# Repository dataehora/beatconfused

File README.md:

# BeatConfused

A small web studio of fast, elegant, install-free music tools. Every tool
is plain HTML, CSS and vanilla JavaScript with the Web Audio API — no build
step, no dependencies, no accounts, works offline after first load.

Live at [beatconfused.com](https://beatconfused.com).

## Tools

| Tool | Path | What it does |
| --- | --- | --- |
| **Metronome** | [`/metronome/`](https://beatconfused.com/metronome/) | Tap tempo, organized time signatures, beat subdivisions, counting modes, sound styles, and pulse / number / pendulum visuals. |
| **Tuner** | [`/tuner/`](https://beatconfused.com/tuner/) | Chromatic instrument tuner with needle, strobe and LED-meter displays, an adjustable A4 reference pitch, historical tuning standards, a test-tone generator, and a spectrum analyser. |
| **Octave Strobe Tuner** | [`/strobetuner/`](https://beatconfused.com/strobetuner/) | Identifies the note being played and shows its tuning across every octave at once on a single strobe disc. |
| **Chromatic Strobe Tuner** | [`/multistrobe/`](https://beatconfused.com/multistrobe/) | One dedicated strobe wheel per note, laid out like a piano keyboard, each with a ring per octave across the 88-key range. |
| **Luthier Tuning** | [`/luthier/`](https://beatconfused.com/luthier/) | Live spectrogram for luthiers and tuners: a slowly decaying live spectrum over a peak-hold record of every frequency, a sustain waterfall, harmonic guides, and a full-range / audible-only toggle. |

## Repository layout

```
index.html            Studio landing page (tool cards + JSON-LD)
styles.css             Landing-page styles
metronome/             Metronome — index.html, script.js, styles.css, Assets/
tuner/                 Tuner — index.html, script.js, styles.css
strobetuner/           Octave Strobe Tuner — index.html, script.js, styles.css
multistrobe/           Chromatic Strobe Tuner — index.html, script.js, styles.css
luthier/               Luthier Tuning (spectrogram) — index.html, script.js, styles.css
etutti/                eTutti (work in progress, unlisted) — Web MIDI page, Teensy firmware/,
                       hardware/ (eTuttino board v0.7 + case SPEC v9), manuais/, models/
binfacevsfarage/       Standalone browser game (not linked from the studio)
shared/                Assets shared across tools
CNAME, robots.txt, sitemap.xml   Hosting + crawl metadata
```

## Metronome controls

### Tempo
- **Slider** / **input field** — smooth or direct BPM entry (40–240)
- **+/- buttons** — step by 5 BPM
- **Tap tempo** — tap the button or press `T` to detect BPM
- **Arrow keys** — Up / Down to adjust BPM

### Beat settings
- **Time signature** — organized simple, compound and odd meters
- **Beat subdivision** — split each beat into more pulses
- **Tempo counting** — beat count, measure + beat, or hidden
- **Beat visual** — pulse, numbers, or pendulum
- **Sound style** — electronic, bossa, jazz, wood, cymbal, cowbell
- **Sound / vibration toggles** and **volume control**

### Keyboard shortcuts
- **Space** — start / stop
- **Arrow Up / Down** — BPM ±5
- **T** — tap tempo

### Custom sounds
Drop `{style}_{accent|beat|subdivision}` audio files (`.mp3`, then `.ogg`,
then `.wav`) into `metronome/Assets/` and they replace the synthesised click
for that combination. Anything not supplied keeps the built-in sound, so the
metronome always has audio even with no custom assets.

## Tuner controls

- **Start Tuner** — vintage-style slide switch above the display; turns the
  microphone on. A "no signal" sign appears below the display after ~3s of
  silence while running.
- **Display** — needle, strobe or LED meter
- **Input Monitor and Test Tone** — collapsed by default; microphone gain
  boost and a live level meter, plus a pure tone (with its own frequency,
  fine-tuning and volume controls) fed straight into the tuner and the
  speakers, no mic needed — the same panel /strobetuner/ and /multistrobe/
  use too
- **Spectrum Analyser** — vintage or modern style
- **Tuning Standard and Reference Pitch** — Equal Temperament plus
  Vallotti, Young II, 1/4-comma meantone and Just Intonation (each built
  from first principles), and an A4 reference from 392–466 Hz with
  historical presets (French Baroque, Baroque, Verdi, Standard, Modern,
  Italian Renaissance)
- **Frequency Table** — every note of an 88-key piano (octaves down the
  rows, notes across the columns) under the selected Tuning Standard and
  Reference Pitch, with a live cents deviation next to whichever note is
  sounding

## Luthier Tuning controls

- **Start Listening** — the same slide switch as the tuners (or `Space`)
- **Full range / Audible only** — everything the microphone captures (up
  to half its sample rate, with infrasound and ultrasound shaded) or just
  20 Hz – 20 kHz
- **Live curve** — the current spectrum; each frequency falls back at the
  **Decay speed** (dB/s) so a note's ring-out stays visible
- **Peak hold** — the pale-blue background graph: the loudest level each
  frequency has reached since the last **Reset peak hold**. **On** keeps
  it until reset; **Temporary** holds each maximum for 2 s, then lets it
  fall at the same Decay speed as the live curve; **Off** hides it
- **Sustain history** — a 12-second waterfall under the display
- **Cursor** — hover / tap for frequency, nearest note, live and peak dB,
  plus dashed guides at 2×, 3×, 4×… to judge inharmonicity
- **Input gain** — boosts quiet instruments

## Technical stack

- **HTML5 / CSS3** — semantic structure, gradients and animations
- **Web Audio API** — high-precision timing, autocorrelation pitch
  detection, Goertzel per-octave analysis for the strobe tools
- **Vanilla JavaScript** — no dependencies, no build step
- **Structured data + crawl files** — JSON-LD, `robots.txt`, `sitemap.xml`

## Development

Everything is static — serve the repo root with any static file server:

```bash
git clone https://github.com/dataehora/beatconfused.git
cd beatconfused
python3 -m http.server 8000
# then open http://localhost:8000/
```

## Deployment

Served via GitHub Pages on the `beatconfused.com` domain (`CNAME`). Any
static host with HTTPS works — no server-side code.

## License

MIT License — feel free to use and modify.

## Contributing

Contributions are welcome. Please open a Pull Request.

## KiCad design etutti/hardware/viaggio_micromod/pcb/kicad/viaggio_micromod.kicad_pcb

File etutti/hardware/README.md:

# eTuttino — PCB design (Hall-effect, velocity-sensitive)

A 44-key chromatic button-accordion controller (C-griff, G3–E6).

- **Keys:** Gateron magnetic (Hall-effect) switches, MX-compatible.
- **Sensing:** a TI DRV5056A3 linear Hall sensor under every key, so the
  firmware knows how far down each key is, and from how fast it went
  down, the note's velocity.
- **Brain:** a Teensy 4.0 with the PJRC Audio Adaptor Board Rev D stacked
  on it.

The firmware is in [`../firmware`](../firmware), the web page is
[beatconfused.com/etutti](https://beatconfused.com/etutti/), and the case
(Seixo / Madeira, SPEC v9; shape frozen since v7) is in [`case/`](case/).

> **Board v0.7 (this one) is made for the SPEC v7–v9 case.** The keys sit
> on the case's hexagonal grid (18.5 mm pitch), and the board takes the
> case's inner outline. The assembly and user manuals in
> [`../manuais`](../manuais/) describe this board, the case and the
> controls board; their pictures come from
> [`manual3d/`](manual3d/) (Blender). Nothing has been built
> yet: only the firmware has run on a real Teensy + Audio Board.

## Ordering (ready to upload)

Generated, routed and checked: KiCad DRC 0 errors, 0 warnings,
0 unconnected; firmware cross-check 44/44.

| File | Upload it as |
| --- | --- |
| [`fab/etuttino_gerbers.zip`](fab/etuttino_gerbers.zip) | **the PCB**: Gerbers + drill files. 2 layers, FR-4, **1.2 mm**, shaped outline (328 × 97 mm bounding box) |
| [`fab/etuttino_bom.csv`](fab/etuttino_bom.csv) + [`fab/etuttino_cpl_bottom.csv`](fab/etuttino_cpl_bottom.csv) | **assembly** (JLCPCB PCBA, *Bottom Side*): every SMD part is on the back |
| [`fab/etuttino_plate_gerbers.zip`](fab/etuttino_plate_gerbers.zip) | **the switch plate**: a copper-less **1.6 mm** FR-4 board with the 14 mm cutouts, cut to the case's plate outline (the case is drawn for 1.6 since SPEC v8) |
| [`fab/etuttino_controls_gerbers.zip`](fab/etuttino_controls_gerbers.zip) | **the controls board**: 2 layers, FR-4 1.6 mm, 41.5 × 25.5 mm, all through-hole (see below) |
| [`case/out/`](case/out/) | **the case** (STEP + STL) and the button caps; see [`case/README.md`](case/README.md) |

The BOM has LCSC numbers for the JLCPCB basic parts. Match the two TI parts
(`DRV5056A3QDBZR`, `CD74HC4067M96`) by manufacturer part number in
JLCPCB's BOM tool. Check every part's rotation in the placement preview
before paying.

## Why the sensors are on the back

The DRV5056 is unipolar: its output only rises when a **south** pole faces
its marked (top) side. Gateron's magnetic switches have the magnet's
**north** pole facing down, so a sensor on the front, facing up, would read
nothing.

On the back, the sensor faces away from the switch. The field reaches it
through the board from behind, and the sensor reads that as positive. A
1.2 mm board keeps the sensor as close to the magnet as that allows.

The A3 variant (30 mV/mT at 3.3 V, about 80 mT before saturation) leaves
headroom against Gateron's ~10 mT at rest and ~90 mT bottomed out. The A4
also works.

## Source files and regenerating

| File | What it is |
| --- | --- |
| [`case/pcb_envelope.py`](case/pcb_envelope.py) → `case/out/pcb_envelope.json` | the room the case leaves for the board: outline (notched round the case's screw bosses), plate outline, bottom-plate pillars, height levels, key centres, the stack's and J3's places. Run with the CadQuery venv (see `case/README.md`) |
| [`generate.py`](generate.py) | reads that envelope. Single source of the key layout and of the sensor → multiplexer map (plain Python 3). Prints the `KEY_INPUT` table for the firmware |
| [`build_pcb.py`](build_pcb.py) | builds and **routes** the KiCad board inside that outline, runs DRC, checks it against the firmware, exports everything in `fab/` |
| [`controls_pcb.py`](controls_pcb.py) | the controls board: places, routes (the same router), DRCs and exports it |
| [`mechanics.py`](mechanics.py) | how far the board bends under a key press on the case's pillars (KiCad's Python, numpy) |
| [`manual3d/`](manual3d/) | the assembly manual's pictures: photo-like renders and numbered line drawings of every step, made in Blender from the case STLs, both KiCad boards (`kicad-cli` GLB) and a library of datasheet-sized parts (`parts.py`). `build.py` runs it all; the visual standard and the balloon numbers are in [`manual3d/STYLE.md`](manual3d/STYLE.md) |
| [`etuttino.pretty/`](etuttino.pretty) | footprint library: `Gateron_Magnetic_MX_1u` (two 1.75 mm peg holes, no centre post, no pins), origin at the switch centre |
| [`kicad/etuttino.kicad_pcb`](kicad/etuttino.kicad_pcb), [`kicad/etuttino_plate.kicad_pcb`](kicad/etuttino_plate.kicad_pcb) | the routed board and the plate |
| `build/etuttino_pcb_preview.svg`, `build/etuttino_keys.csv`, `build/etuttino_plate.dxf` | preview; each key's switch, sensor, multiplexer channel, Teensy pin, note and X/Y; the plate as DXF (for aluminium) |

After a case change, rebuild in this order:

```bash
C:/Users/julia/.venvs/cadquery/Scripts/python.exe case/case.py
C:/Users/julia/.venvs/cadquery/Scripts/python.exe case/pcb_envelope.py
python generate.py
"C:/Program Files/KiCad/10.0/bin/python.exe" build_pcb.py
"C:/Program Files/KiCad/10.0/bin/python.exe" mechanics.py
```

Each routing attempt takes about four minutes. The router is greedy: if
a net can't be routed, the script starts again with that net first, up to
20 times. `DEFAULT_ROUTE_FIRST` keeps the order that worked
(`OUT_U41,OUT_U42,GND,LED_R,LED_G_DRV,OUT_U34` for v0.6 and v0.7).

`build_pcb.py` exits with an error if any of these happens:

- DRC finds a problem.
- Anything is left unconnected.
- A part on the back sits over one of the bottom plate's pillars.
- A key doesn't reach the multiplexer channel and Teensy pin that the
  firmware's tables give.

It writes the routed channels into the sketch's `KEY_INPUT`.

## Layout

Chromatic accordion, C-griff, on a **hexagonal grid**: every button is
**18.5 mm** from its six neighbours, and the rows are 18.5 × cos 30° =
**16.02 mm** apart.

- Each key along a row is a **minor third (3 semitones)** above the
  previous one. A diagonal step to the next row is **one semitone**.
- Row 4 repeats row 1's notes from A3 to C6, on row 2's columns.
- **Row 1 is nearest the player.** It is at the front edge, which is the
  bottom of KiCad's top view.
- The same switches also play **B-griff**: the web page's C/B-griff
  switch sends CC 24, and the firmware swaps rows 1 and 3. The PCB does
  not change.

| Row | Keys | Notes | y (mm) |
| --- | --- | --- | --- |
| 1 | 11 | A3 C4 D♯4 F♯4 A4 C5 D♯5 F♯5 A5 C6 D♯6 | 74.03 |
| 2 | 12 | G3 A♯3 C♯4 E4 G4 A♯4 C♯5 E5 G5 A♯5 C♯6 E6 | 58.01 |
| 3 | 11 | G♯3 B3 D4 F4 G♯4 B4 D5 F5 G♯5 B5 D6 | 41.99 |
| 4 | 10 | A3 C4 D♯4 F♯4 A4 C5 D♯5 F♯5 A5 C6 | 25.97 |

**Coordinates** are the case SPEC's. x is measured from the case's left
face, y towards the player. That is KiCad's top view as it stands.

**The board** is the case's inner cavity less 0.5 mm, notched round the
nine screw columns. It fits both the Seixo (2.5 mm walls) and the Madeira
(4 mm). On the left it runs under the interface area, where the Teensy +
Audio Board stack sits in the back corner:

- USB faces the case's left face, where a short cable goes to the panel
  socket.
- The VIN row is at the back.
- The stack is ~13 mm tall in the eTuttino and 10 mm or less in the
  eTuttiChorus.
- The Audio Board sits ~3 mm above the PCB on its header legs.
- These positions come from `case/fit_check.py`.

**Held by the case:**

- Under the keys, the lid presses the plate's edge, the plate presses
  the switches, and the switches' bottom housings press the board.
- Under the interface, two M2 screws come up from below. They go through
  the bottom plate's pillars at (30; 60) and (12; 70) and through the
  board's holes H1 and H2, with a nut on top. These two pillars are
  Ø6, with a counterbore for the head. The router keeps copper 3.5 mm
  away from both holes.
- The board rests on **64 pillars** of the bottom plate, one at the
  centre of every triangle of three neighbouring keys (10.7 mm from each
  sensor). The case has 3 more pillars under the interface.
- Under a firm 3 N press the board sags **0.044 mm** at worst (E6, row 2)
  and 0.009 mm on average. Check with `mechanics.py`.
- No part on the back may sit over a pillar. `build_pcb.py` checks this.

## Electrical

**Per key (back side):**

- A DRV5056A3 (SOT-23) straight under the switch centre.
- Its 100 nF capacitor just behind it.
- A 3.3 V bus behind each key row and a GND bus in front of it (0.4 mm).
- The sensor output drops to a via and is routed to its multiplexer.

**Multiplexers:** three CD74HC4067 (SOIC-24), all on the back.

- U51 sits in front of the interface, left of rows 1 and 2. It serves row 1
  and the left end of row 2.
- U52 and U53 lie sideways in the strip behind row 4 and serve the rest,
  split left and right.
- The router picks each key's channel; see `build/etuttino_keys.csv`.
- The address lines are shared, and Enable is tied to GND.

| Net | Teensy pin |
| --- | --- |
| SEL0–SEL3 (multiplexer address S0–S3) | 0, 1, 2, 3 |
| COM0 / COM1 / COM2 (U51 / U52 / U53 output) | 14 (A0) / 15 (A1) / 16 (A2) |
| VIN (USB 5 V) → regulator | VIN |
| GND | GND (both rows) |
| LED_R_DRV / LED_G_DRV → 330 Ω (R1 / R2) → J3 | 4 (red), 5 (green) |
| POT → J3 | 22 (A8) |
| ENC_A / ENC_B / ENC_SW → J3 | 17 / 9 / 6 |

**J3, the controls board.** A JST PH 2.0 mm 8-pin vertical header, in front
of the Audio Board, under the interface lid. A short 1:1 cable goes up
to the controls board.

| Pin | Net |
| --- | --- |
| 1 | VCC 3.3 V |
| 2 | GND |
| 3 | POT |
| 4 | ENC_A |
| 5 | ENC_B |
| 6 | ENC_SW |
| 7 | LED_R |
| 8 | LED_G |

The firmware reads the pot as the volume and the encoder as the
instrument selector (see `../firmware/README.md`). With no controls board
plugged in, the pot input is ignored. Pin 6 is the Audio Board's optional
memory-chip select, so leave that chip unfitted.

## Controls board

`controls_pcb.py` → `kicad/etuttino_controls.kicad_pcb` and
`fab/etuttino_controls_gerbers.zip`. KiCad DRC 0 / 0 / 0. In case
coordinates it spans x 14.5–56, y 35.5–61. It hangs under the interface lid
on two posts of the case, with M2 screws through H1 and H2 from below. Its
top faces the lid:

| Ref | Part | Where |
| --- | --- | --- |
| RV1 | Alps RK09K vertical pot, 10 k linear, 6 mm shaft L = 15 | shaft at (20; 45): volume |
| SW1 | Alps EC11E encoder with push switch, L = 15 | shaft at (37; 45): instrument |
| D1 | 3 mm red/green LED, common cathode | (52; 45), on a spacer up to the lid's hole (Seixo) or just under the light pipe (Madeira); `case/FIT_CHECK.md` gives the spacer length |
| J1 | JST PH B8B-PH-K vertical, on the back, facing down | the cable drops straight to the main board's J3, pin for pin |

The encoder's common and one switch leg go to GND. The Teensy's pull-ups
do the rest. The LED's 330 Ω resistors are on the main board.

**Power LED.** A 3 mm red/green bicolour LED (common cathode) on the
controls board, under the lid's LED hole, or the Madeira's light pipe:

- orange while the keys are read at power-up;
- green while playing;
- blinking red on an error.

**Power.** 44 sensors draw about 260 mA, more than the Teensy's own 3.3 V
pin should give. An AMS1117-3.3 (U60, SOT-223) makes a separate 3.3 V rail
from VIN for the sensors and the multiplexers:

- it sits on the back between the Teensy pin rows;
- it has 10 µF in and 22 µF out.

**Pins kept clear of:**

- 7, 8, 18–21, 23: the Audio Board's audio and I²C;
- 10–13: its SD card;
- 15 is its *optional* volume pot, which is not fitted on a stock board, so
  COM1 can use it.

**Routing:** two layers.

- Per-key wiring and the row buses are laid deterministically.
- Everything else goes through a small A* grid router in `build_pcb.py`:
  0.254 mm grid aligned to the Teensy pins, both layers, vias, KiCad's
  clearances, 0.5 mm from the board's outline.
- KiCad's DRC then checks the result independently.

## Teensy + Audio Board mounting

- Two rows of 14 holes (2.54 mm pitch, 15.24 mm apart), with the 0–12 row
  at the front and the VIN–13 row at the back. The silkscreen marks
  "GND"/"0", "VIN"/"23" and "< USB".
- Two 1×14 extra-long male headers (≈ 20–25 mm pins) join all three
  boards: the Teensy is soldered straight onto the Audio Board, the
  header's plastic as the only spacer, and the long legs go on down
  through these holes with the Audio Board ~3 mm above the PCB, soldered
  and trimmed on the back.
- Stack height, from under the Audio Board to the top of the Teensy's
  USB: the case was checked with 13 mm and has room for 16.9 mm (Seixo) /
  16.4 mm (Madeira); the eTuttiChorus needs 10 mm or less, to clear the
  screen.
- USB goes to the panel socket through a short cable with a 90° micro-USB
  plug. The panel headphone jack is wired to the Audio Board's headphone
  pads.

## Bill of materials (main board)

| Qty | Part | Notes |
| --- | --- | --- |
| 44 | Gateron KS-20 magnetic switch (north pole down) | plate-mounted, **not soldered**: no pins, two plastic pegs |
| 44 | DRV5056A3QDBZR, SOT-23 | back, under each switch |
| 47 | 100 nF 0805 | one per sensor + one per multiplexer |
| 3 | CD74HC4067M96, SOIC-24 | back |
| 1 | AMS1117-3.3, SOT-223 | back |
| 1 + 1 | 10 µF, 22 µF 0805 | regulator input / output |
| 2 | 330 Ω 0805 | LED resistors R1, R2 (back) |
| 1 | JST PH 8-pin vertical header (B8B-PH-K-S) + a 1:1 PH cable, ~60 mm | J3, to the controls board |
| 2 + 2 | M2 × 10 mm screw + M2 nut | through the bottom plate's two thick pillars and H1 / H2 |
| 1 | Teensy 4.0 + PJRC Audio Adaptor Board **Rev D** | + 2 × 1×14 extra-long male headers |
| 1 | switch plate | 1.6 mm FR-4 from `fab/etuttino_plate_gerbers.zip`, or 1.5 mm aluminium from `build/etuttino_plate.dxf` |
| 44 | button caps | 3D-printed from `case/out/keycap_*.stl` (26 natural / C-F, 18 sharp) |

**Controls board:**

| Qty | Part |
| --- | --- |
| 1 | Alps RK09K1130 (or equivalent) vertical pot, 10 k linear, 15 mm shaft |
| 1 | Alps EC11E with push switch, **15 pulses / 15 detents**, 15 mm shaft (`ENC_STEPS_PER_DETENT` = 4 in the firmware; 2 for a 30-detent one) |
| 1 | 3 mm LED, red/green, common cathode, + a ≈ 4 mm LED spacer (Seixo); the Madeira has a 3 mm light pipe in the lid instead |
| 1 | JST PH B8B-PH-K-S |
| 2 | M2 × 5 mm self-tapping screws, into the lid's posts |
| 2 | knobs, Ø9, for 6 mm shafts |

The case is listed in [`case/README.md`](case/README.md).

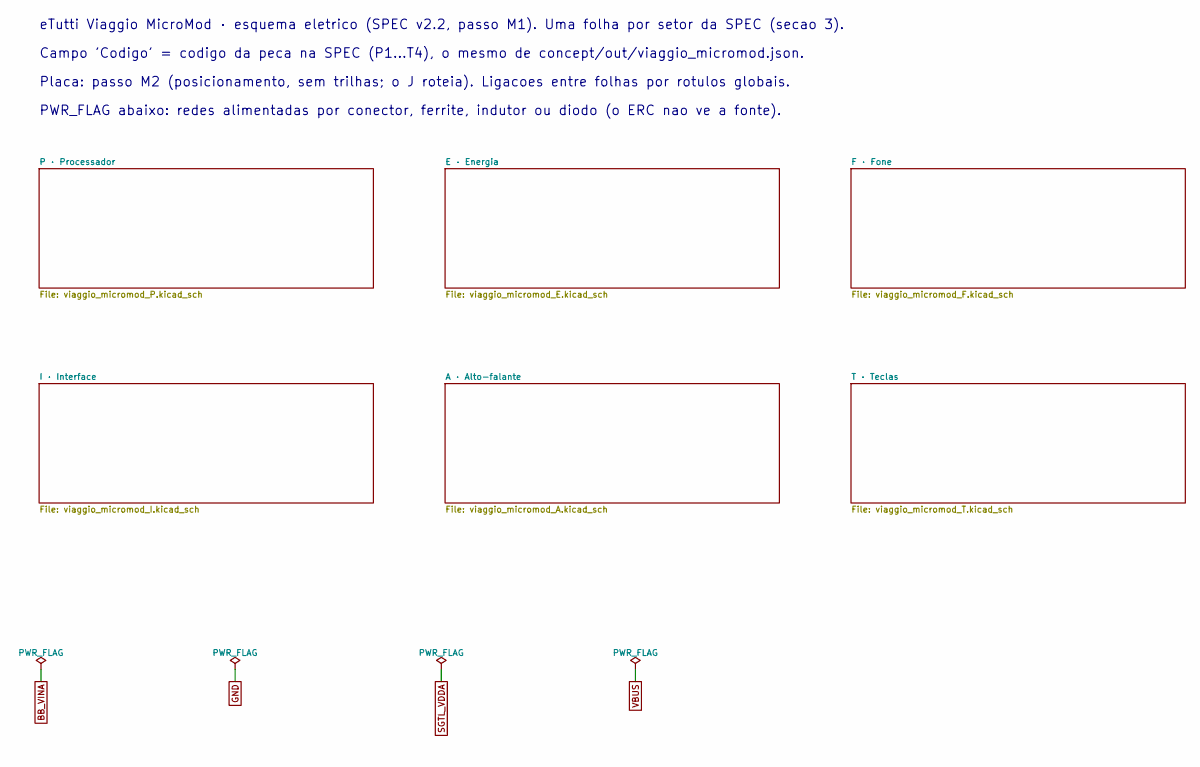
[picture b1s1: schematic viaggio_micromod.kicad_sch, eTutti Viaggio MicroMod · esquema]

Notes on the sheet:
eTutti Viaggio MicroMod · esquema eletrico (SPEC v2.2, passo M1). Uma folha por setor da SPEC (secao 3).
Campo 'Codigo' = codigo da peca na SPEC (P1...T4), o mesmo de concept/out/viaggio_micromod.json.
Placa: passo M2 (posicionamento, sem trilhas; o J roteia). Ligacoes entre folhas por rotulos globais.
PWR_FLAG abaixo: redes alimentadas por conector, ferrite, indutor ou diodo (o ERC nao ve a fonte).

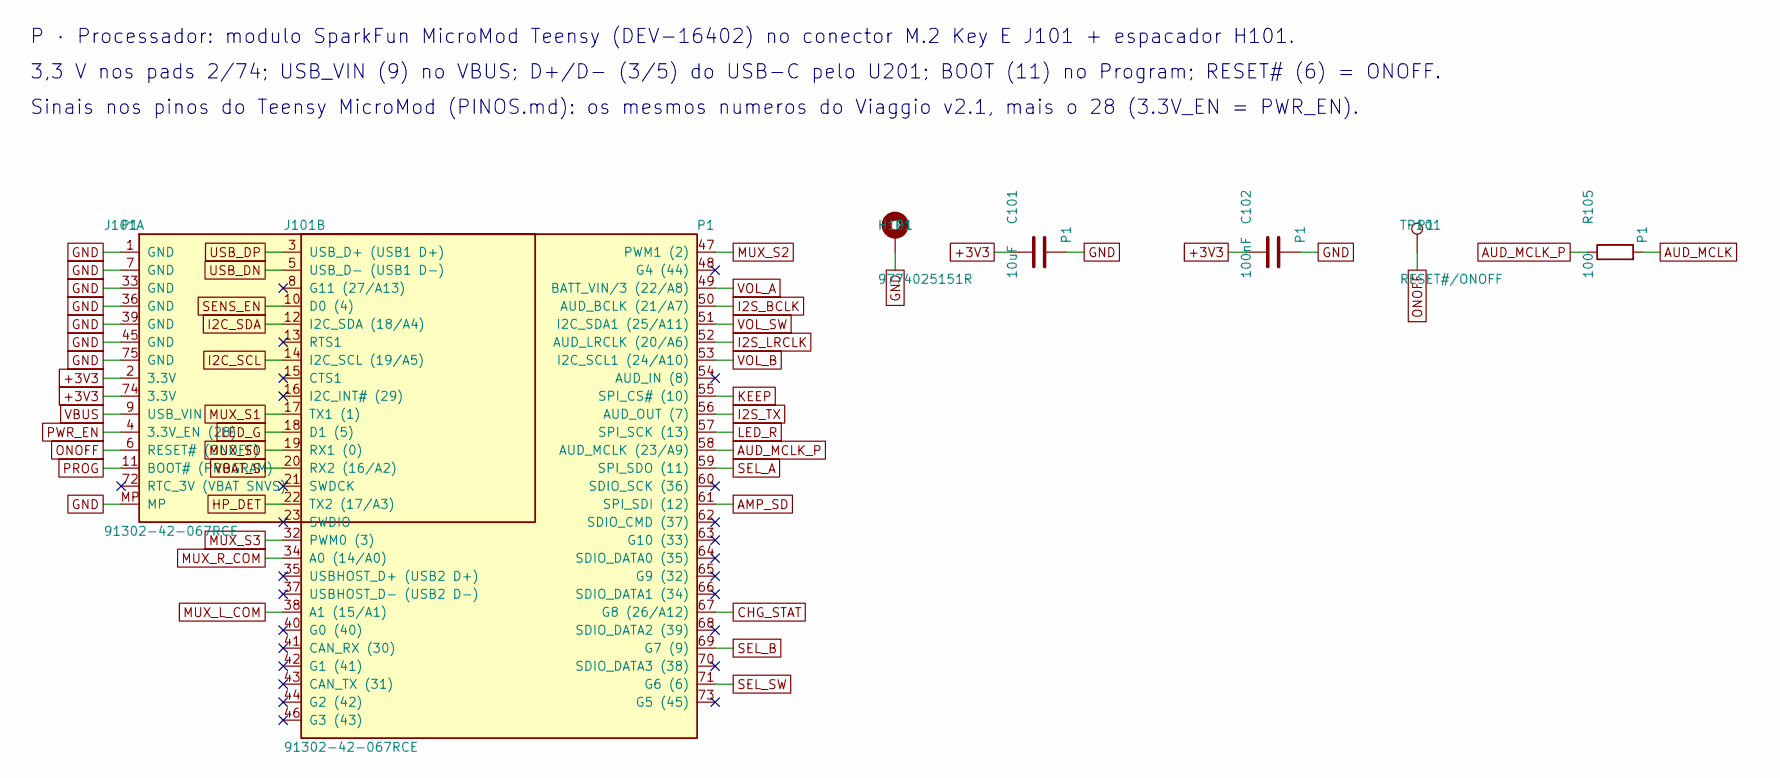
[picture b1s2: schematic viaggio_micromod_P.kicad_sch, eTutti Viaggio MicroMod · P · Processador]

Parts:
C101: 10uF; C_0805_2012Metric; LCSC C15850
C102: 100nF; C_0402_1005Metric; LCSC C1525
H101: 9774025151R; Standoff_SMD_M2.5_H2.5
J101: 91302-42-067RCE; M.2_E_H4.2_UMAX_91302-42-067; LCSC C48985906
R105: 100; R_0402_1005Metric; LCSC C25076
TP101: RESET#/ONOFF; TestPoint_Pad_D1.5mm

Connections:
+3V3: C101.1, C102.1, J101.2 (3.3V), J101.74 (3.3V); also elsewhere on the board
AMP_SD: J101.61 (SPI_SDI (12)); also elsewhere on the board
AUD_MCLK: R105.2; also elsewhere on the board
AUD_MCLK_P: J101.58 (AUD_MCLK (23/A9)), R105.1
CHG_STAT: J101.67 (G8 (26/A12)); also elsewhere on the board
GND: C101.2, C102.2, H101.1, J101.1 (GND), J101.7 (GND), J101.33 (GND), J101.36 (GND), J101.39 (GND), J101.45 (GND), J101.75 (GND), J101.MP; also elsewhere on the board
HP_DET: J101.22 (TX2 (17/A3)); also elsewhere on the board
I2C_SCL: J101.14 (I2C_SCL (19/A5)); also elsewhere on the board
I2C_SDA: J101.12 (I2C_SDA (18/A4)); also elsewhere on the board
I2S_BCLK: J101.50 (AUD_BCLK (21/A7)); also elsewhere on the board
I2S_LRCLK: J101.52 (AUD_LRCLK (20/A6)); also elsewhere on the board
I2S_TX: J101.56 (AUD_OUT (7)); also elsewhere on the board
KEEP: J101.55 (SPI_CS# (10)); also elsewhere on the board
LED_G: J101.18 (D1 (5)); also elsewhere on the board
LED_R: J101.57 (SPI_SCK (13)); also elsewhere on the board
MUX_L_COM: J101.38 (A1 (15/A1)); also elsewhere on the board
MUX_R_COM: J101.34 (A0 (14/A0)); also elsewhere on the board
MUX_S0: J101.19 (RX1 (0)); also elsewhere on the board
MUX_S1: J101.17 (TX1 (1)); also elsewhere on the board
MUX_S2: J101.47 (PWM1 (2)); also elsewhere on the board
MUX_S3: J101.32 (PWM0 (3)); also elsewhere on the board
ONOFF: J101.6 (RESET# (ONOFF)), TP101.1; also elsewhere on the board
PROG: J101.11 (BOOT# (PROGRAM)); also elsewhere on the board
PWR_EN: J101.4 (3.3V_EN (28)); also elsewhere on the board
SEL_A: J101.59 (SPI_SDO (11)); also elsewhere on the board
SEL_B: J101.69 (G7 (9)); also elsewhere on the board
SEL_SW: J101.71 (G6 (6)); also elsewhere on the board
SENS_EN: J101.10 (D0 (4)); also elsewhere on the board
USB_DN: J101.5 (USB_D- (USB1 D-)); also elsewhere on the board
USB_DP: J101.3 (USB_D+ (USB1 D+)); also elsewhere on the board
VBAT_S: J101.20 (RX2 (16/A2)); also elsewhere on the board
VBUS: J101.9 (USB_VIN); also elsewhere on the board
VOL_A: J101.49 (BATT_VIN/3 (22/A8)); also elsewhere on the board
VOL_B: J101.53 (I2C_SCL1 (24/A10)); also elsewhere on the board
VOL_SW: J101.51 (I2C_SDA1 (25/A11)); also elsewhere on the board

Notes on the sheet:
P · Processador: modulo SparkFun MicroMod Teensy (DEV-16402) no conector M.2 Key E J101 + espacador H101.
3,3 V nos pads 2/74; USB_VIN (9) no VBUS; D+/D- (3/5) do USB-C pelo U201; BOOT (11) no Program; RESET# (6) = ONOFF.
Sinais nos pinos do Teensy MicroMod (PINOS.md): os mesmos numeros do Viaggio v2.1, mais o 28 (3.3V_EN = PWR_EN).

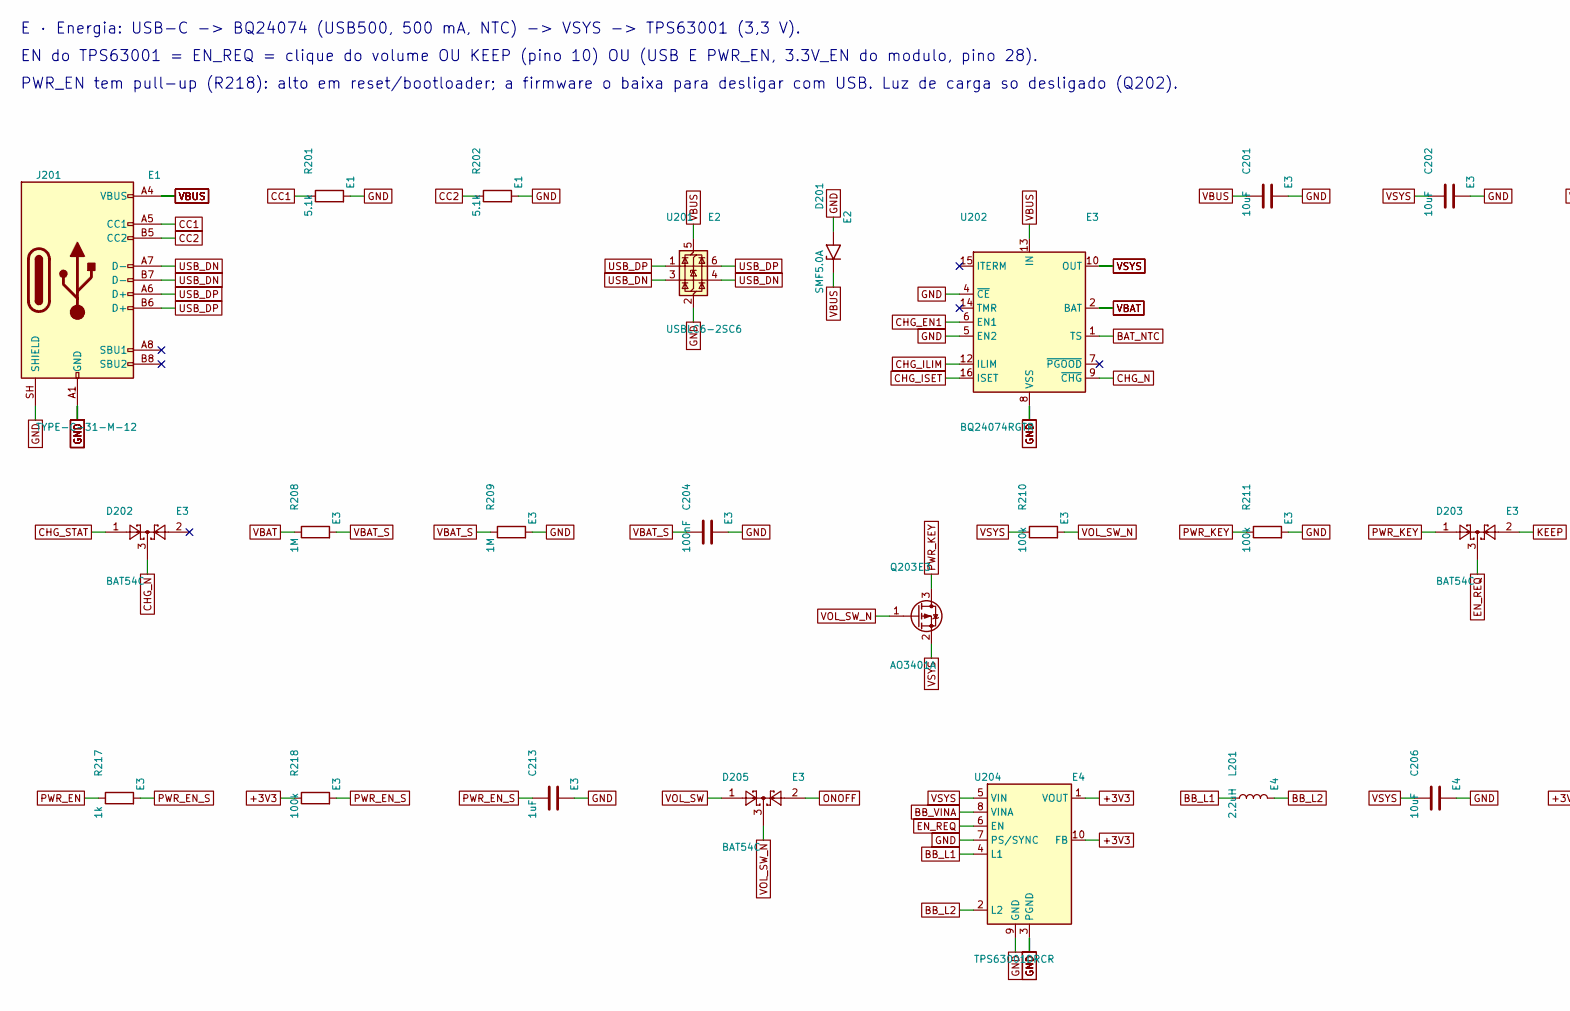
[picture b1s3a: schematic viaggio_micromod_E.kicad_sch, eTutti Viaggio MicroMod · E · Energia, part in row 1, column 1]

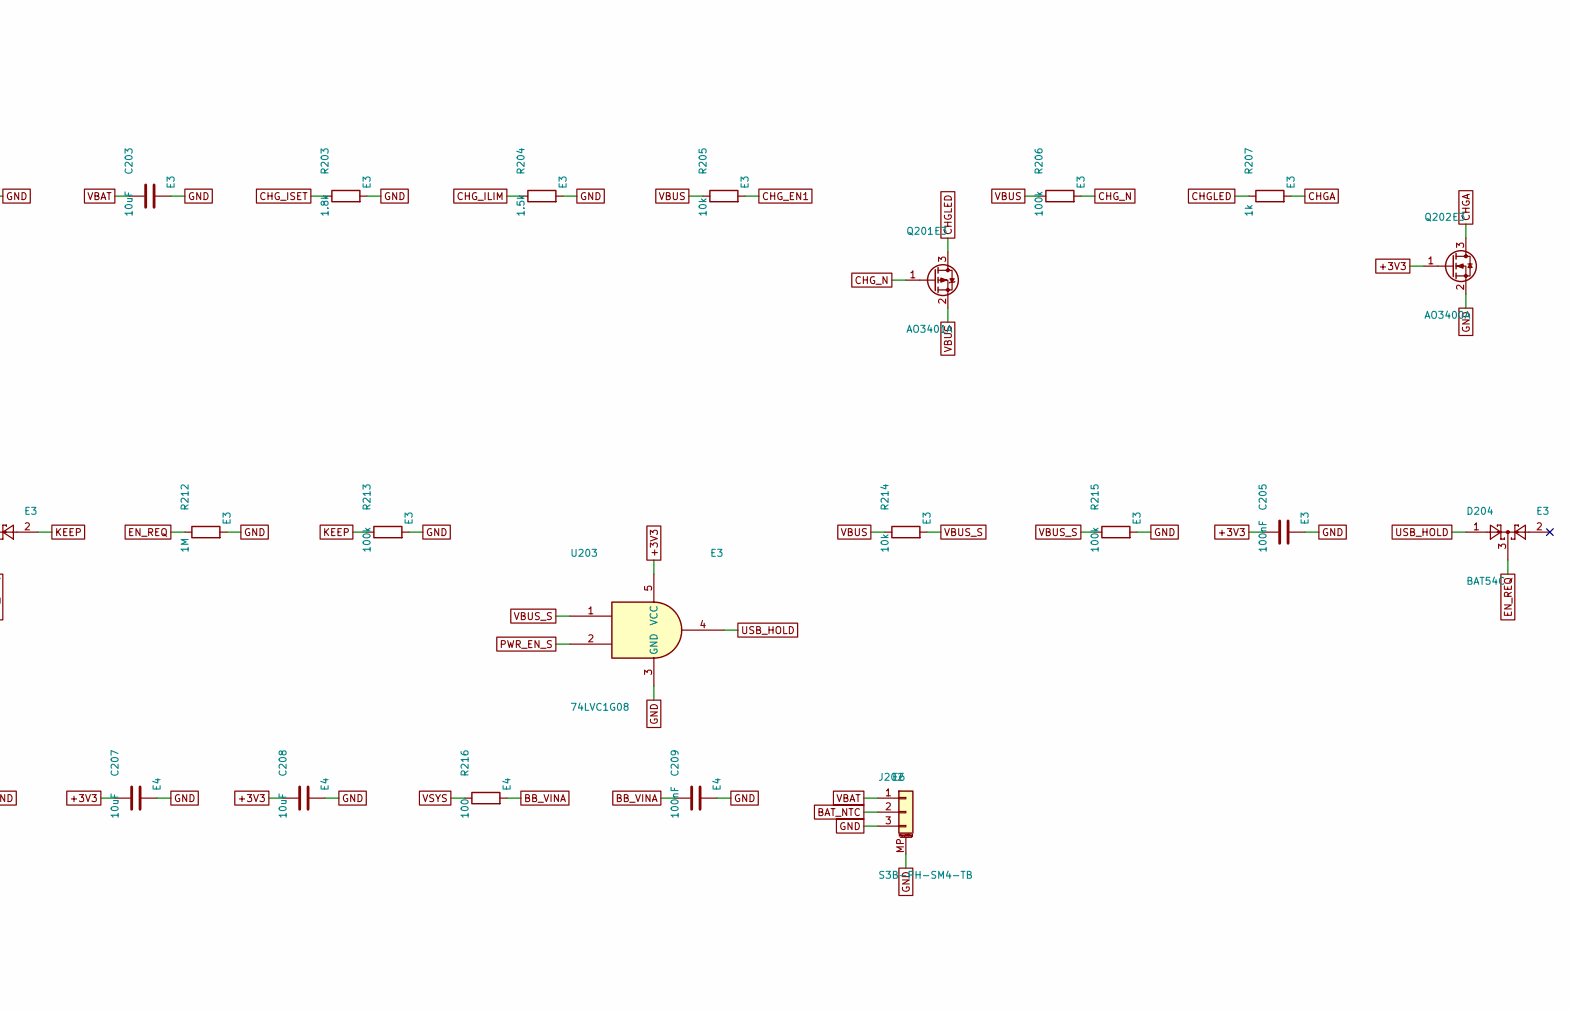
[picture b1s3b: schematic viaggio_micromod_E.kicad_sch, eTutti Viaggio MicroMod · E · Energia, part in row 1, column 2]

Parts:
C201, C202, C203, C206, C207, C208: 10uF; C_0805_2012Metric; LCSC C15850
C204, C205, C209: 100nF; C_0402_1005Metric; LCSC C1525
C213: 1uF; C_0402_1005Metric; LCSC C52923
D201: SMF5.0A; D_SOD-123F; LCSC C151296
D202, D203, D204, D205: BAT54C; SOT-23; LCSC C134405
J201: TYPE-C-31-M-12; USB_C_Receptacle_HRO_TYPE-C-31-M-12; LCSC C165948
J202: S3B-PH-SM4-TB; JST_PH_S3B-PH-SM4-TB_1x03-1MP_P2.00mm_Horizontal; LCSC C265101
L201: 2.2uH; L_Changjiang_FNR4020S; LCSC C167825
Q201, Q203: AO3401A; SOT-23; LCSC C15127
Q202: AO3400A; SOT-23; LCSC C20917
R201, R202: 5.1k; R_0402_1005Metric; LCSC C25905
R203: 1.8k; R_0402_1005Metric; LCSC C25811
R204: 1.5k; R_0402_1005Metric; LCSC C25867
R205, R214: 10k; R_0402_1005Metric; LCSC C25744
R206, R210, R211, R213, R215, R218: 100k; R_0402_1005Metric; LCSC C25741
R207, R217: 1k; R_0402_1005Metric; LCSC C11702
R208, R209, R212: 1M; R_0402_1005Metric; LCSC C26083
R216: 100; R_0402_1005Metric; LCSC C25076
U201: USBLC6-2SC6; SOT-23-6; LCSC C7519
U202: BQ24074RGTR; VQFN-16-1EP_3x3mm_P0.5mm_EP1.6x1.6mm; LCSC C54313
U203: 74LVC1G08; SOT-23-5; LCSC C7666
U204: TPS63001DRCR; Texas_DRC0010J; LCSC C28060

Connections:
+3V3: C205.1, C207.1, C208.1, Q202.1 (G), R218.1, U203.5 (VCC), U204.1 (VOUT), U204.10 (FB); also elsewhere on the board
BAT_NTC: J202.2, U202.1 (TS)
BB_L1: L201.1, U204.4 (L1)
BB_L2: L201.2, U204.2 (L2)
BB_VINA: C209.1, R216.2, U204.8 (VINA)
CC1: J201.A5 (CC1), R201.1
CC2: J201.B5 (CC2), R202.1
CHGA: Q202.3 (D), R207.2; also elsewhere on the board
CHGLED: Q201.3 (D), R207.1
CHG_EN1: R205.2, U202.6 (EN1)
CHG_ILIM: R204.1, U202.12 (ILIM)
CHG_ISET: R203.1, U202.16 (ISET)
CHG_N: D202.3, Q201.1 (G), R206.2, U202.9 (~CHG)
CHG_STAT: D202.1; also elsewhere on the board
EN_REQ: D203.3, D204.3, R212.1, U204.6 (EN)
GND: C201.2, C202.2, C203.2, C204.2, C205.2, C206.2, C207.2, C208.2, C209.2, C213.2, D201.2 (A2), J201.A1 (GND), J201.A12 (GND), J201.B1 (GND), J201.B12 (GND), J201.SH (SHIELD), J202.3, J202.MP (MountPin), Q202.2 (S), R201.2, R202.2, R203.2, R204.2, R209.2, R211.2, R212.2, R213.2, R215.2, U201.2 (GND), U202.4 (~CE), U202.5 (EN2), U202.8 (VSS), U202.17 (VSS), U203.3 (GND), U204.3 (PGND), U204.7 (PS/SYNC), U204.9 (GND), U204.11 (PGND); also elsewhere on the board
KEEP: D203.2, R213.1; also elsewhere on the board
ONOFF: D205.2; also elsewhere on the board
PWR_EN: R217.1; also elsewhere on the board
PWR_EN_S: C213.1, R217.2, R218.2, U203.2
PWR_KEY: D203.1, Q203.3 (D), R211.1
USB_DN: J201.A7 (D-), J201.B7 (D-), U201.3 (I/O2), U201.4 (I/O2); also elsewhere on the board
USB_DP: J201.A6 (D+), J201.B6 (D+), U201.1 (I/O1), U201.6 (I/O1); also elsewhere on the board
USB_HOLD: D204.1, U203.4
VBAT: C203.1, J202.1, R208.1, U202.2 (BAT), U202.3 (BAT)
VBAT_S: C204.1, R208.2, R209.1; also elsewhere on the board
VBUS: C201.1, D201.1 (A1), J201.A4 (VBUS), J201.A9 (VBUS), J201.B4 (VBUS), J201.B9 (VBUS), Q201.2 (S), R205.1, R206.1, R214.1, U201.5 (VBUS), U202.13 (IN); also elsewhere on the board
VBUS_S: R214.2, R215.1, U203.1
VOL_SW: D205.1; also elsewhere on the board
VOL_SW_N: D205.3, Q203.1 (G), R210.2; also elsewhere on the board
VSYS: C202.1, C206.1, Q203.2 (S), R210.1, R216.1, U202.10 (OUT), U202.11 (OUT), U204.5 (VIN); also elsewhere on the board

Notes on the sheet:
E · Energia: USB-C -> BQ24074 (USB500, 500 mA, NTC) -> VSYS -> TPS63001 (3,3 V).
EN do TPS63001 = EN_REQ = clique do volume OU KEEP (pino 10) OU (USB E PWR_EN, 3.3V_EN do modulo, pino 28).
PWR_EN tem pull-up (R218): alto em reset/bootloader; a firmware o baixa para desligar com USB. Luz de carga so desligado (Q202).

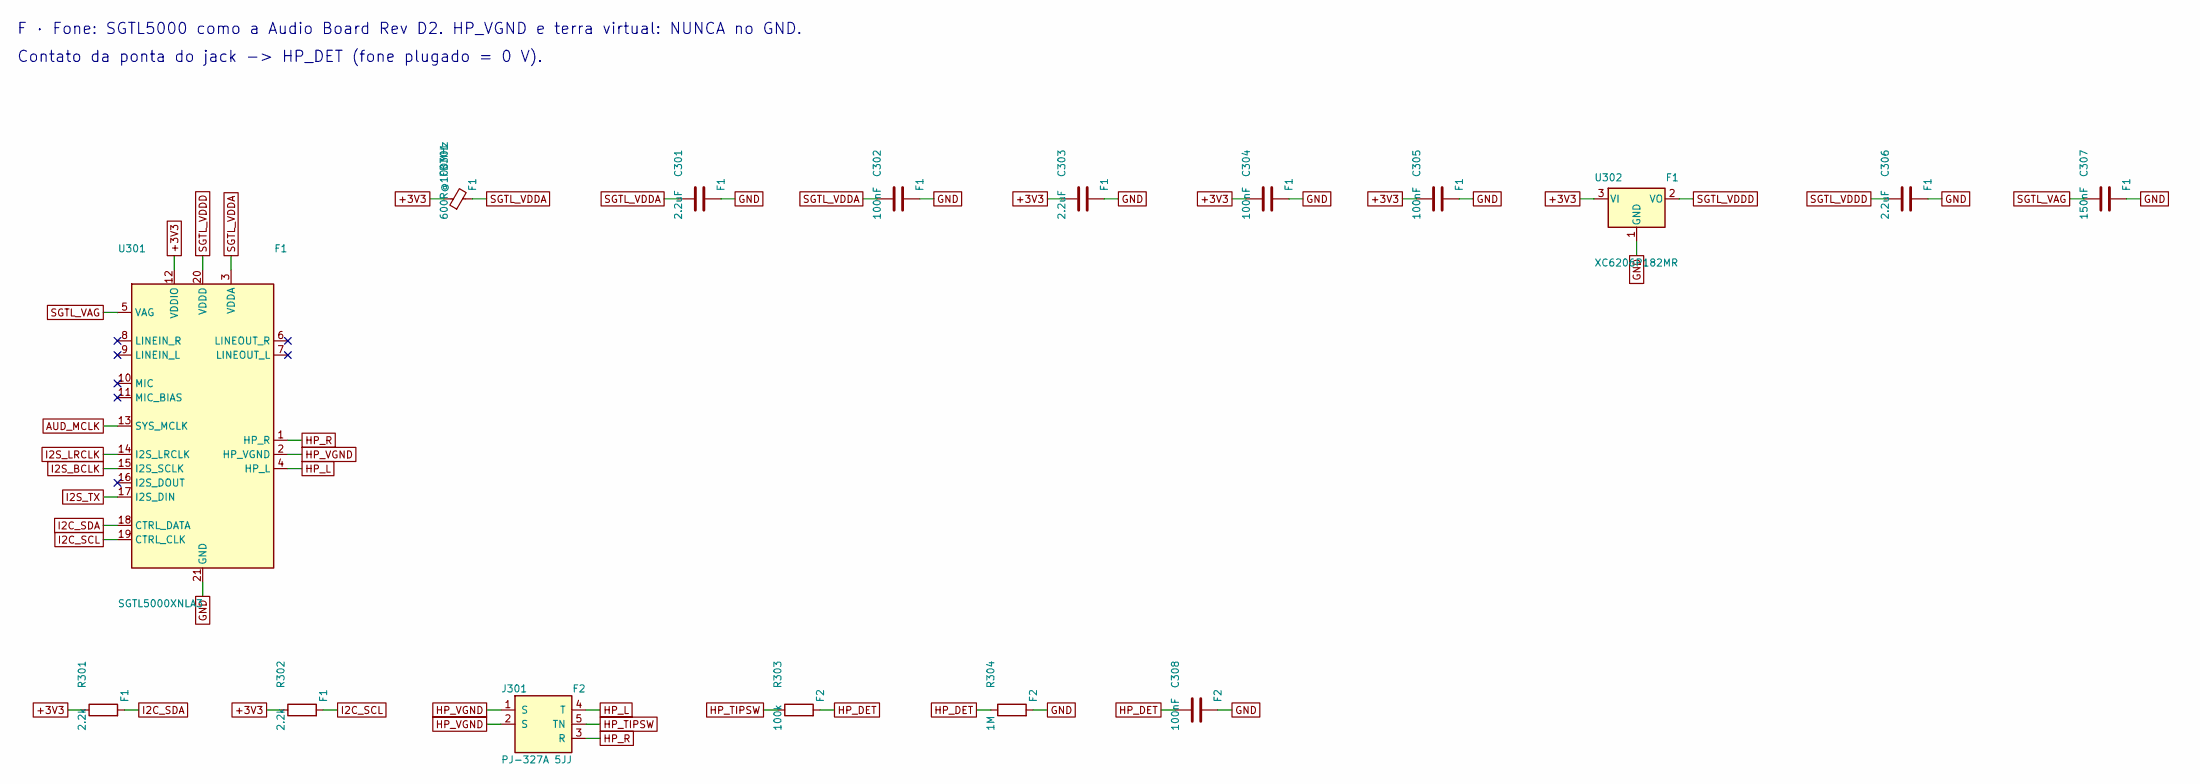
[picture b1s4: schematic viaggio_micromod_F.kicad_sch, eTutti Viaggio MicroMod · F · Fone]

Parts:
C301, C303, C306: 2.2uF; C_0402_1005Metric; LCSC C12530
C302, C304, C305, C308: 100nF; C_0402_1005Metric; LCSC C1525
C307: 150nF; C_0402_1005Metric
FB301: 600R@100MHz; L_0603_1608Metric
J301: PJ-327A 5JJ; Jack_3.5mm_PJ-327A_SMD; LCSC C668605
R301, R302: 2.2k; R_0402_1005Metric; LCSC C25879
R303: 100k; R_0402_1005Metric; LCSC C25741
R304: 1M; R_0402_1005Metric; LCSC C26083
U301: SGTL5000XNLA3; QFN-20-1EP_3x3mm_P0.4mm_EP1.65x1.65mm; LCSC C511764
U302: XC6206P182MR; SOT-23-3; LCSC C347373

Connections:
+3V3: C303.1, C304.1, C305.1, FB301.1, R301.1, R302.1, U301.12 (VDDIO), U302.3 (VI); also elsewhere on the board
AUD_MCLK: U301.13 (SYS_MCLK); also elsewhere on the board
GND: C301.2, C302.2, C303.2, C304.2, C305.2, C306.2, C307.2, C308.2, R304.2, U301.21 (GND), U302.1 (GND); also elsewhere on the board
HP_DET: C308.1, R303.2, R304.1; also elsewhere on the board
HP_L: J301.4 (T), U301.4 (HP_L)
HP_R: J301.3 (R), U301.1 (HP_R)
HP_TIPSW: J301.5 (TN), R303.1
HP_VGND: J301.1 (S), J301.2 (S), U301.2 (HP_VGND)
I2C_SCL: R302.2, U301.19 (CTRL_CLK); also elsewhere on the board
I2C_SDA: R301.2, U301.18 (CTRL_DATA); also elsewhere on the board
I2S_BCLK: U301.15 (I2S_SCLK); also elsewhere on the board
I2S_LRCLK: U301.14 (I2S_LRCLK); also elsewhere on the board
I2S_TX: U301.17 (I2S_DIN); also elsewhere on the board
SGTL_VAG: C307.1, U301.5 (VAG)
SGTL_VDDA: C301.1, C302.1, FB301.2, U301.3 (VDDA)
SGTL_VDDD: C306.1, U301.20 (VDDD), U302.2 (VO)

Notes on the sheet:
F · Fone: SGTL5000 como a Audio Board Rev D2. HP_VGND e terra virtual: NUNCA no GND.
Contato da ponta do jack -> HP_DET (fone plugado = 0 V).

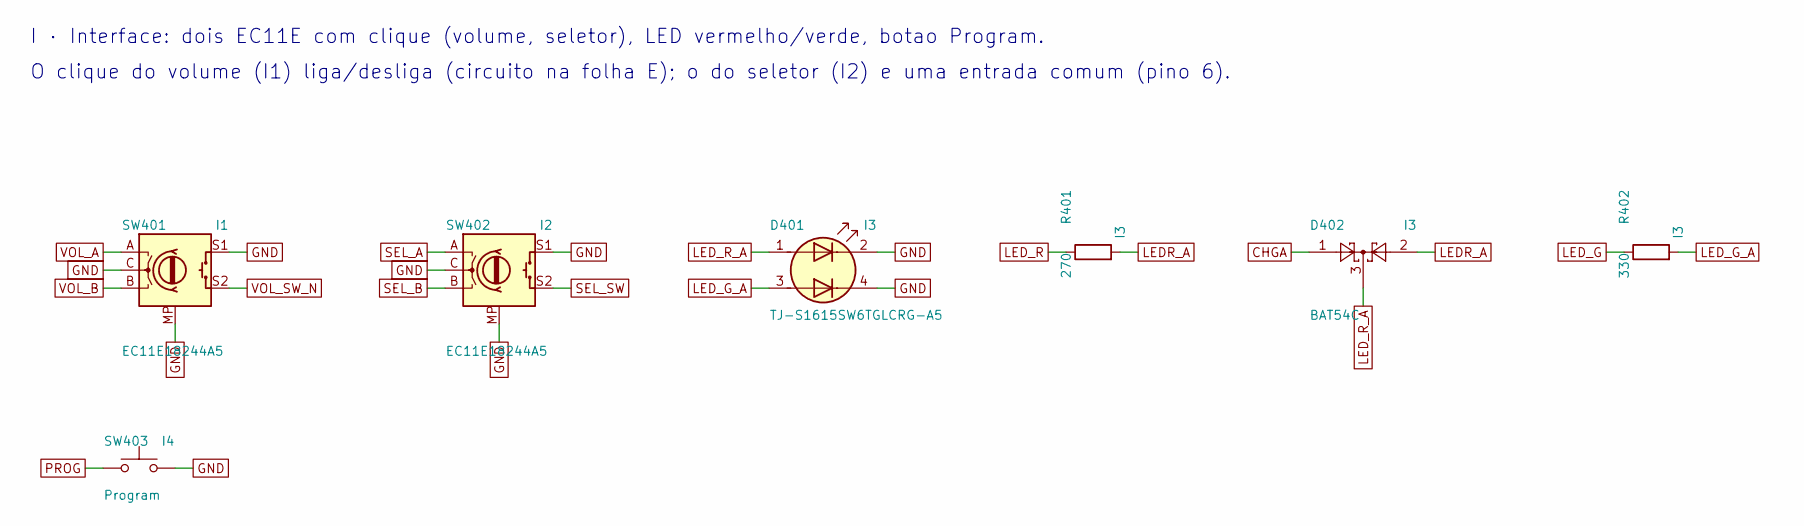
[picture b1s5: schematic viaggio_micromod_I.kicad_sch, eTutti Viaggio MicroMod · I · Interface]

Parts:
D401: TJ-S1615SW6TGLCRG-A5; LED_1615_RG_4pad; LCSC C273605
D402: BAT54C; SOT-23; LCSC C134405
R401: 270; R_0402_1005Metric; LCSC C25190
R402: 330; R_0402_1005Metric; LCSC C25104
SW401, SW402: EC11E18244A5; RotaryEncoder_Alps_EC11E-Switch_Vertical_H20mm; LCSC C255515
SW403: Program; SW_Push_1P1T_XKB_TS-1187A; LCSC C318884

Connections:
CHGA: D402.1; also elsewhere on the board
GND: D401.2 (K1), D401.4 (K2), SW401.C, SW401.MP, SW401.S1, SW402.C, SW402.MP, SW402.S1, SW403.2; also elsewhere on the board
LEDR_A: D402.2, R401.2
LED_G: R402.1; also elsewhere on the board
LED_G_A: D401.3 (A2), R402.2
LED_R: R401.1; also elsewhere on the board
LED_R_A: D401.1 (A1), D402.3
PROG: SW403.1; also elsewhere on the board
SEL_A: SW402.A; also elsewhere on the board
SEL_B: SW402.B; also elsewhere on the board
SEL_SW: SW402.S2; also elsewhere on the board
VOL_A: SW401.A; also elsewhere on the board
VOL_B: SW401.B; also elsewhere on the board
VOL_SW_N: SW401.S2; also elsewhere on the board

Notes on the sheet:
I · Interface: dois EC11E com clique (volume, seletor), LED vermelho/verde, botao Program.
O clique do volume (I1) liga/desliga (circuito na folha E); o do seletor (I2) e uma entrada comum (pino 6).

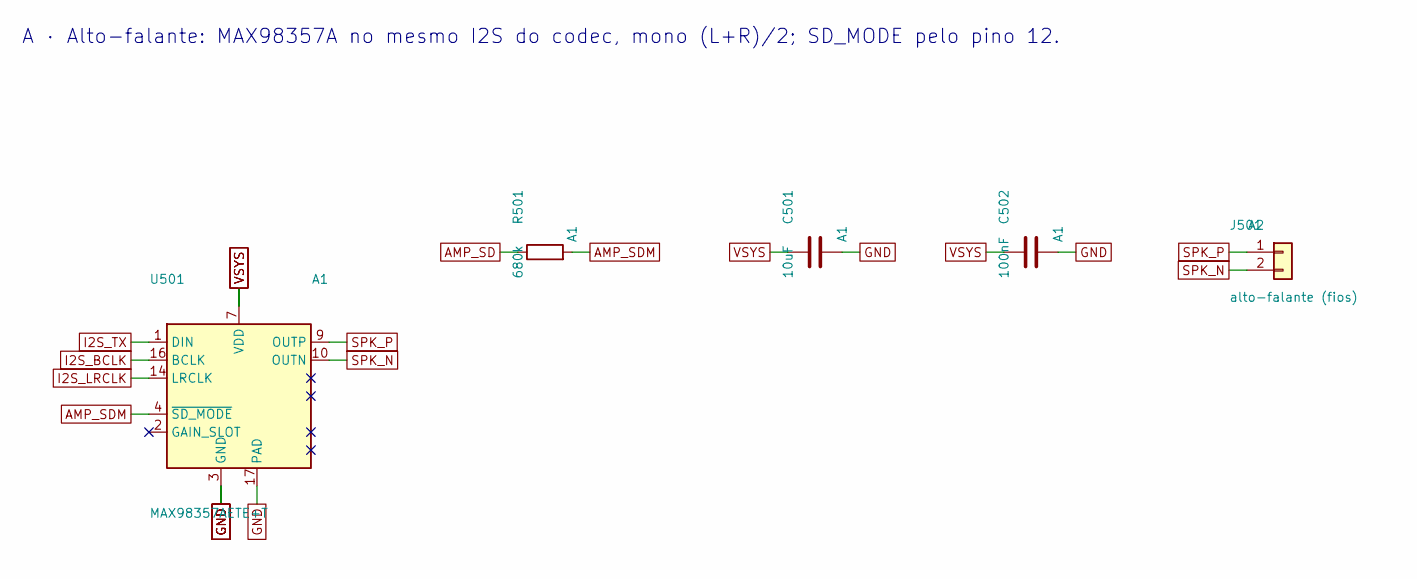
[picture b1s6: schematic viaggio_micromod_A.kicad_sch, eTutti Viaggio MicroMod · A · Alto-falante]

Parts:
C501: 10uF; C_0805_2012Metric; LCSC C15850
C502: 100nF; C_0402_1005Metric; LCSC C1525
J501: alto-falante (fios); SolderWire-0.127sqmm_1x02_P3.7mm_D0.48mm_OD1mm
R501: 680k; R_0402_1005Metric
U501: MAX98357AETE+T; TQFN-16-1EP_3x3mm_P0.5mm_EP1.23x1.23mm; LCSC C910544

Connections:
AMP_SD: R501.1; also elsewhere on the board
AMP_SDM: R501.2, U501.4 (~SD_MODE)
GND: C501.2, C502.2, U501.3 (GND), U501.11 (GND), U501.15 (GND), U501.17 (PAD); also elsewhere on the board
I2S_BCLK: U501.16 (BCLK); also elsewhere on the board
I2S_LRCLK: U501.14 (LRCLK); also elsewhere on the board
I2S_TX: U501.1 (DIN); also elsewhere on the board
SPK_N: J501.2, U501.10 (OUTN)
SPK_P: J501.1, U501.9 (OUTP)
VSYS: C501.1, C502.1, U501.7 (VDD), U501.8 (VDD); also elsewhere on the board

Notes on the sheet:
A · Alto-falante: MAX98357A no mesmo I2S do codec, mono (L+R)/2; SD_MODE pelo pino 12.
